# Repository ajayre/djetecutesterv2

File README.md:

# djetecutesterv2
D-Jetronic ECU Tester V2

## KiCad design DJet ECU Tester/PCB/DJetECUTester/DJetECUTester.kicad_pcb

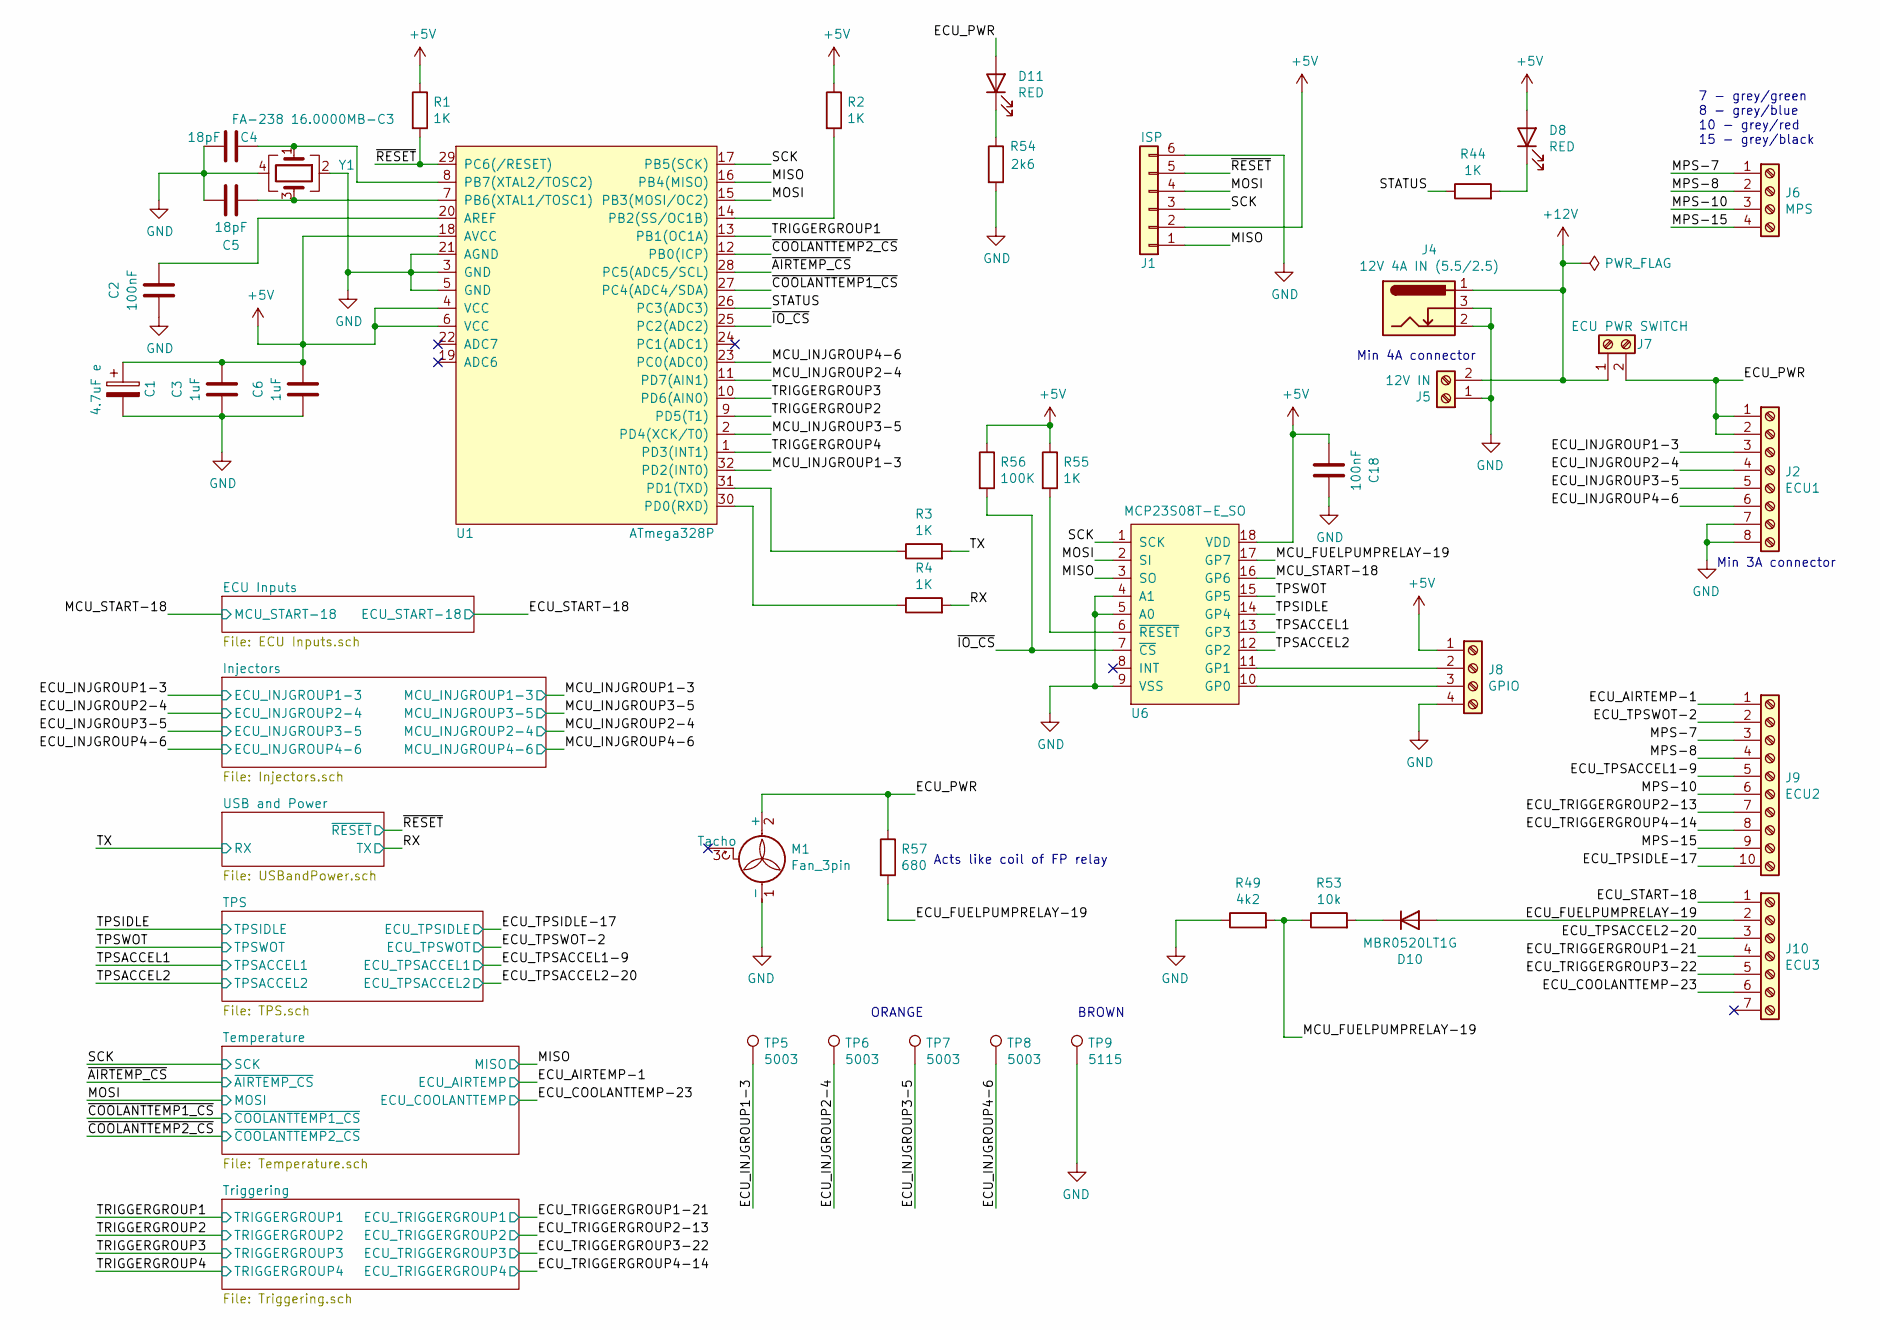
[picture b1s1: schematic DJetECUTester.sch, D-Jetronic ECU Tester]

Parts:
C1: 4.7uF e; CP_Elec_4x5.8
C2, C18: 100nF; C_0805_2012Metric
C3, C6: 1uF; C_0805_2012Metric
C4, C5: 18pF; C_0805_2012Metric
D8, D11: RED; LED_PLCC-2
D10: MBR0520LT1G; SOD-123
J1: ISP; PinHeader_2x03_P2.54mm_Vertical
J2: ECU1; PhoenixContact_COMBICON_PT_8
J4: 12V 4A IN (5.5/2.5); BarrelJack_Wuerth_6941xx301002
J5: 12V IN; PhoenixContact_COMBICON_MKDSN_2
J6: MPS; PhoenixContact_COMBICON_PT_4
J7: ECU PWR SWITCH; PhoenixContact_COMBICON_MKDSN_2
J8: GPIO; PhoenixContact_COMBICON_PT_4
J9: ECU2; PhoenixContact_COMBICON_PT_10
J10: ECU3; PhoenixContact_COMBICON_PT_7
M1: Fan_3pin; FanPinHeader_1x03_P2.54mm_Vertical
R1, R2, R3, R4, R44, R55: 1K; R_0805_2012Metric
R49: 4k2; R_0805_2012Metric
R53: 10k; R_0805_2012Metric
R54: 2k6; R_0805_2012Metric
R56: 100K; R_0805_2012Metric
R57: 680; R_1206_3216Metric
TP5, TP6, TP7, TP8: 5003; Keystone-Minature-Test-Point-Colored-500x-511x
TP9: 5115; Keystone-Minature-Test-Point-Colored-500x-511x
U1: ATmega328P; LQFP-32_7x7mm_P0.8mm
U6: MCP23S08T-E_SO; SOIC-18W_7.5x11.6mm_P1.27mm
Y1: FA-238 16.0000MB-C3; FA-238

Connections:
+5V: C1.1, C3.1, C6.1, C18.2, D8.2 (A), J1.2, J8.1, R1.1, R2.1, R55.1, R56.1, U1.4 (VCC), U1.6 (VCC), U1.18 (AVCC), U6.18 (VDD); also elsewhere on the board
+12V: J4.1, J5.2, J7.1; also elsewhere on the board
/ECU_AIRTEMP-1: J9.1; also elsewhere on the board
/ECU_COOLANTTEMP-23: J10.6; also elsewhere on the board
/ECU_FUELPUMPRELAY-19: D10.2 (A), J10.2, R57.2
/ECU_INJGROUP1-3: J2.3, TP5.1; also elsewhere on the board
/ECU_INJGROUP2-4: J2.4, TP6.1; also elsewhere on the board
/ECU_INJGROUP3-5: J2.5, TP7.1; also elsewhere on the board
/ECU_INJGROUP4-6: J2.6, TP8.1; also elsewhere on the board
/ECU_PWR: D11.2 (A), J2.1, J2.2, J7.2, M1.2 (+), R57.1
/ECU_START-18: J10.1; also elsewhere on the board
/ECU_TPSACCEL1-9: J9.5; also elsewhere on the board
/ECU_TPSACCEL2-20: J10.3; also elsewhere on the board
/ECU_TPSIDLE-17: J9.10; also elsewhere on the board
/ECU_TPSWOT-2: J9.2; also elsewhere on the board
/ECU_TRIGGERGROUP1-21: J10.4; also elsewhere on the board
/ECU_TRIGGERGROUP2-13: J9.7; also elsewhere on the board
/ECU_TRIGGERGROUP3-22: J10.5; also elsewhere on the board
/ECU_TRIGGERGROUP4-14: J9.8; also elsewhere on the board
/MCU_FUELPUMPRELAY-19: R49.2, R53.1, U6.17 (GP7)
/MCU_INJGROUP1-3: U1.32 (PD2(INT0)); also elsewhere on the board
/MCU_INJGROUP2-4: U1.11 (PD7(AIN1)); also elsewhere on the board
/MCU_INJGROUP3-5: U1.2 (PD4(XCK/T0)); also elsewhere on the board
/MCU_INJGROUP4-6: U1.23 (PC0(ADC0)); also elsewhere on the board
/MCU_START-18: U6.16 (GP6); also elsewhere on the board
/MISO: J1.1, U1.16 (PB4(MISO)), U6.3 (SO); also elsewhere on the board
/MOSI: J1.4, U1.15 (PB3(MOSI/OC2)), U6.2 (SI); also elsewhere on the board
/MPS-7: J6.1, J9.3
/MPS-8: J6.2, J9.4
/MPS-10: J6.3, J9.6
/MPS-15: J6.4, J9.9
/RX: R4.2; also elsewhere on the board
/SCK: J1.3, U1.17 (PB5(SCK)), U6.1 (SCK); also elsewhere on the board
/STATUS: R44.1, U1.26 (PC3(ADC3))
/TPSACCEL1: U6.13 (GP3); also elsewhere on the board
/TPSACCEL2: U6.12 (GP2); also elsewhere on the board
/TPSIDLE: U6.14 (GP4); also elsewhere on the board
/TPSWOT: U6.15 (GP5); also elsewhere on the board
/TRIGGERGROUP1: U1.13 (PB1(OC1A)); also elsewhere on the board
/TRIGGERGROUP2: U1.9 (PD5(T1)); also elsewhere on the board
/TRIGGERGROUP3: U1.10 (PD6(AIN0)); also elsewhere on the board
/TRIGGERGROUP4: U1.1 (PD3(INT1)); also elsewhere on the board
/TX: R3.2; also elsewhere on the board
/~AIRTEMP_CS: U1.28 (PC5(ADC5/SCL)); also elsewhere on the board
/~COOLANTTEMP1_CS: U1.27 (PC4(ADC4/SDA)); also elsewhere on the board
/~COOLANTTEMP2_CS: U1.12 (PB0(ICP)); also elsewhere on the board
/~IO_CS: R56.2, U1.25 (PC2(ADC2)), U6.7 (~CS)
/~RESET: J1.5, R1.2, U1.29 (PC6(/RESET)); also elsewhere on the board
GND: C1.2, C2.2, C3.2, C4.2, C5.1, C6.2, C18.1, J1.6, J2.7, J2.8, J4.2, J4.3, J5.1, J8.4, M1.1 (-), R49.1, R54.2, TP9.1, U1.3 (GND), U1.5 (GND), U1.21 (AGND), U6.4 (A1), U6.5 (A0), U6.9 (VSS), Y1.2, Y1.4; also elsewhere on the board
unnamed: C2.1, U1.20 (AREF)
unnamed: C4.1, U1.8 (PB7(XTAL2/TOSC2)), Y1.1
unnamed: C5.2, U1.7 (PB6(XTAL1/TOSC1)), Y1.3
unnamed: D8.1 (K), R44.2
unnamed: D10.1 (K), R53.2
unnamed: D11.1 (K), R54.1
unnamed: J8.2, U6.11 (GP1)
unnamed: J8.3, U6.10 (GP0)
unnamed: R2.2, U1.14 (PB2(SS/OC1B))
unnamed: R3.1, U1.31 (PD1(TXD))
unnamed: R4.1, U1.30 (PD0(RXD))
unnamed: R55.2, U6.6 (~RESET)

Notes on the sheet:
7 - grey/green 8 - grey/blue 10 - grey/red 15 - grey/black
BROWN
ORANGE
Min 4A connector
Min 3A connector
Acts like coil of FP relay

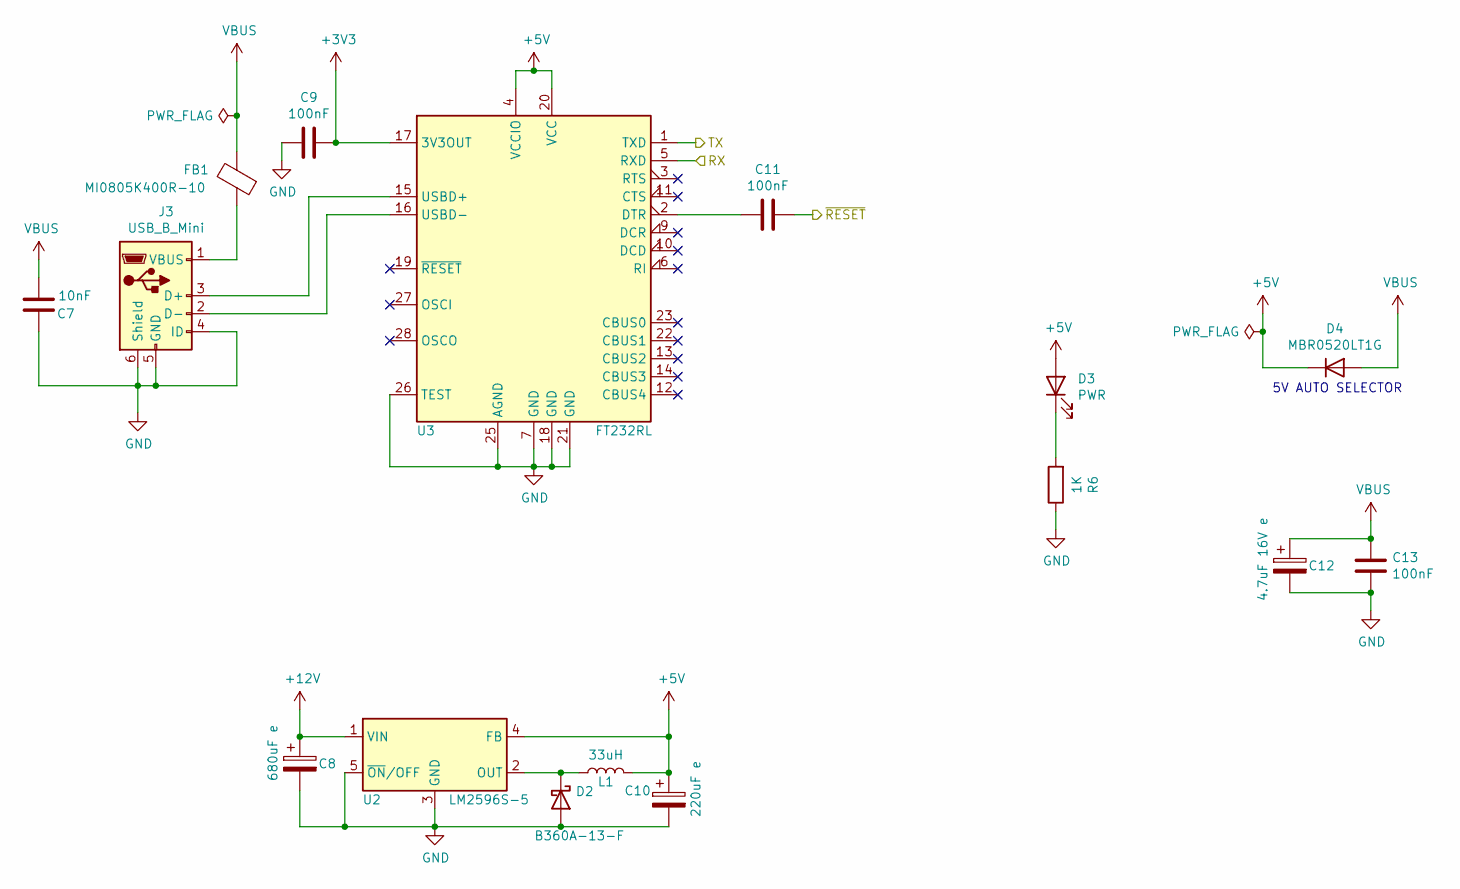
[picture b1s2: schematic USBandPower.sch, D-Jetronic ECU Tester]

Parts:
C7: 10nF; C_0805_2012Metric
C8: 680uF e; CP_Elec_10x10.5
C9, C11, C13: 100nF; C_0805_2012Metric
C10: 220uF e; CP_Elec_8x6.5
C12: 4.7uF 16V e; CP_Elec_4x5.8
D2: B360A-13-F; D_SMA
D3: PWR; LED_PLCC-2
D4: MBR0520LT1G; SOD-123
FB1: MI0805K400R-10; R_0805_2012Metric
J3: USB_B_Mini; USB_Mini-B_Wuerth_65100516121_Horizontal
L1: 33uH; Wurth-WE-LQS-Inductor
R6: 1K; R_0805_2012Metric
U2: LM2596S-5; TO-263-5_TabPin3
U3: FT232RL; SSOP-28_5.3x10.2mm_P0.65mm

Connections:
+3V3: C9.1, U3.17 (3V3OUT)
+5V: C10.1, D3.2 (A), D4.1 (K), L1.2, U2.4 (FB), U3.4 (VCCIO), U3.20 (VCC); also elsewhere on the board
+12V: C8.1, U2.1 (VIN); also elsewhere on the board
/RX: U3.1 (TXD); also elsewhere on the board
/TX: U3.5 (RXD); also elsewhere on the board
/~RESET: C11.1; also elsewhere on the board
GND: C7.1, C8.2, C9.2, C10.2, C12.2, C13.2, D2.2 (A), J3.4 (ID), J3.5 (GND), J3.6 (Shield), R6.1, U2.3 (GND), U2.5 (~ON~/OFF), U3.7 (GND), U3.18 (GND), U3.21 (GND), U3.25 (AGND), U3.26 (TEST); also elsewhere on the board
unnamed: C11.2, U3.2 (DTR)
unnamed: D2.1 (K), L1.1, U2.2 (OUT)
unnamed: D3.1 (K), R6.2
unnamed: FB1.1, J3.1 (VBUS)
unnamed: J3.2 (D-), U3.16 (USBD-)
unnamed: J3.3 (D+), U3.15 (USBD+)
VBUS: C7.2, C12.1, C13.1, D4.2 (A), FB1.2

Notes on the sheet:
5V AUTO SELECTOR

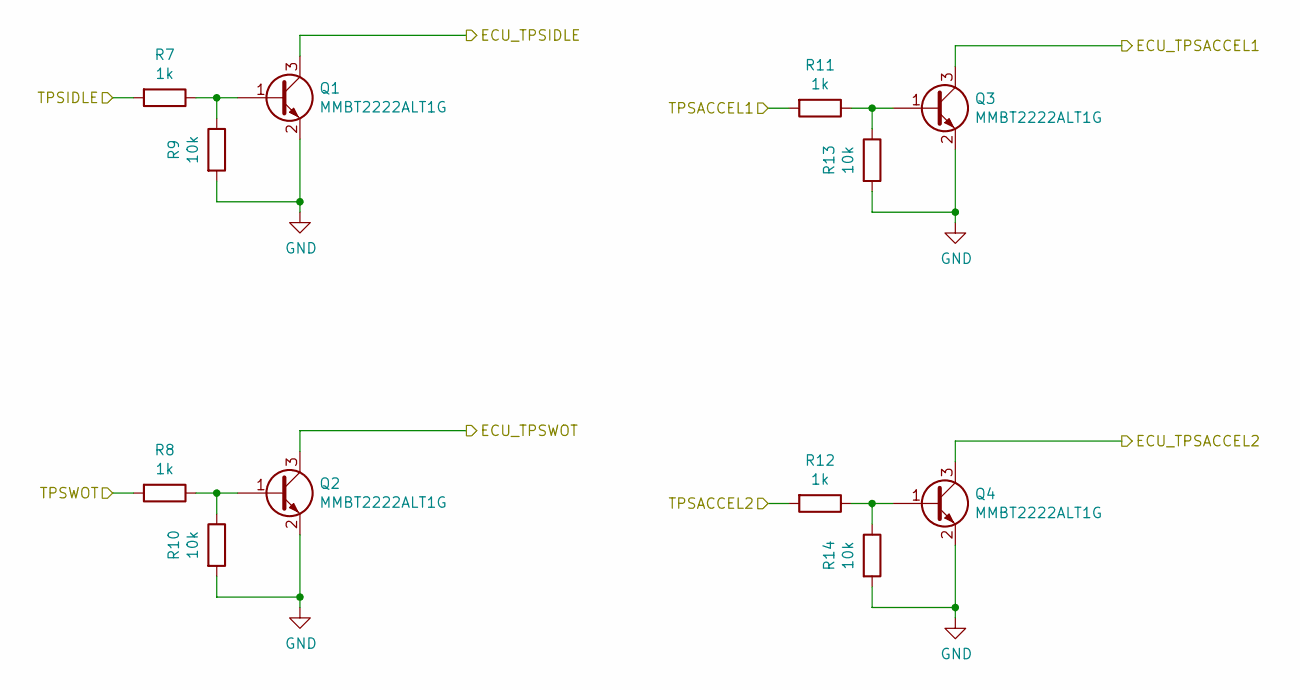
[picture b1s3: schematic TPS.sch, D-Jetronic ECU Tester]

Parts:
Q1, Q2, Q3, Q4: MMBT2222ALT1G; SOT-23
R7, R8, R11, R12: 1k; R_0805_2012Metric
R9, R10, R13, R14: 10k; R_0805_2012Metric

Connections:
/ECU_TPSACCEL1-9: Q3.3 (C); also elsewhere on the board
/ECU_TPSACCEL2-20: Q4.3 (C); also elsewhere on the board
/ECU_TPSIDLE-17: Q1.3 (C); also elsewhere on the board
/ECU_TPSWOT-2: Q2.3 (C); also elsewhere on the board
/TPSACCEL1: R11.2; also elsewhere on the board
/TPSACCEL2: R12.2; also elsewhere on the board
/TPSIDLE: R7.2; also elsewhere on the board
/TPSWOT: R8.2; also elsewhere on the board
GND: Q1.2 (E), Q2.2 (E), Q3.2 (E), Q4.2 (E), R9.2, R10.2, R13.2, R14.2; also elsewhere on the board
unnamed: Q1.1 (B), R7.1, R9.1
unnamed: Q2.1 (B), R8.1, R10.1
unnamed: Q3.1 (B), R11.1, R13.1
unnamed: Q4.1 (B), R12.1, R14.1

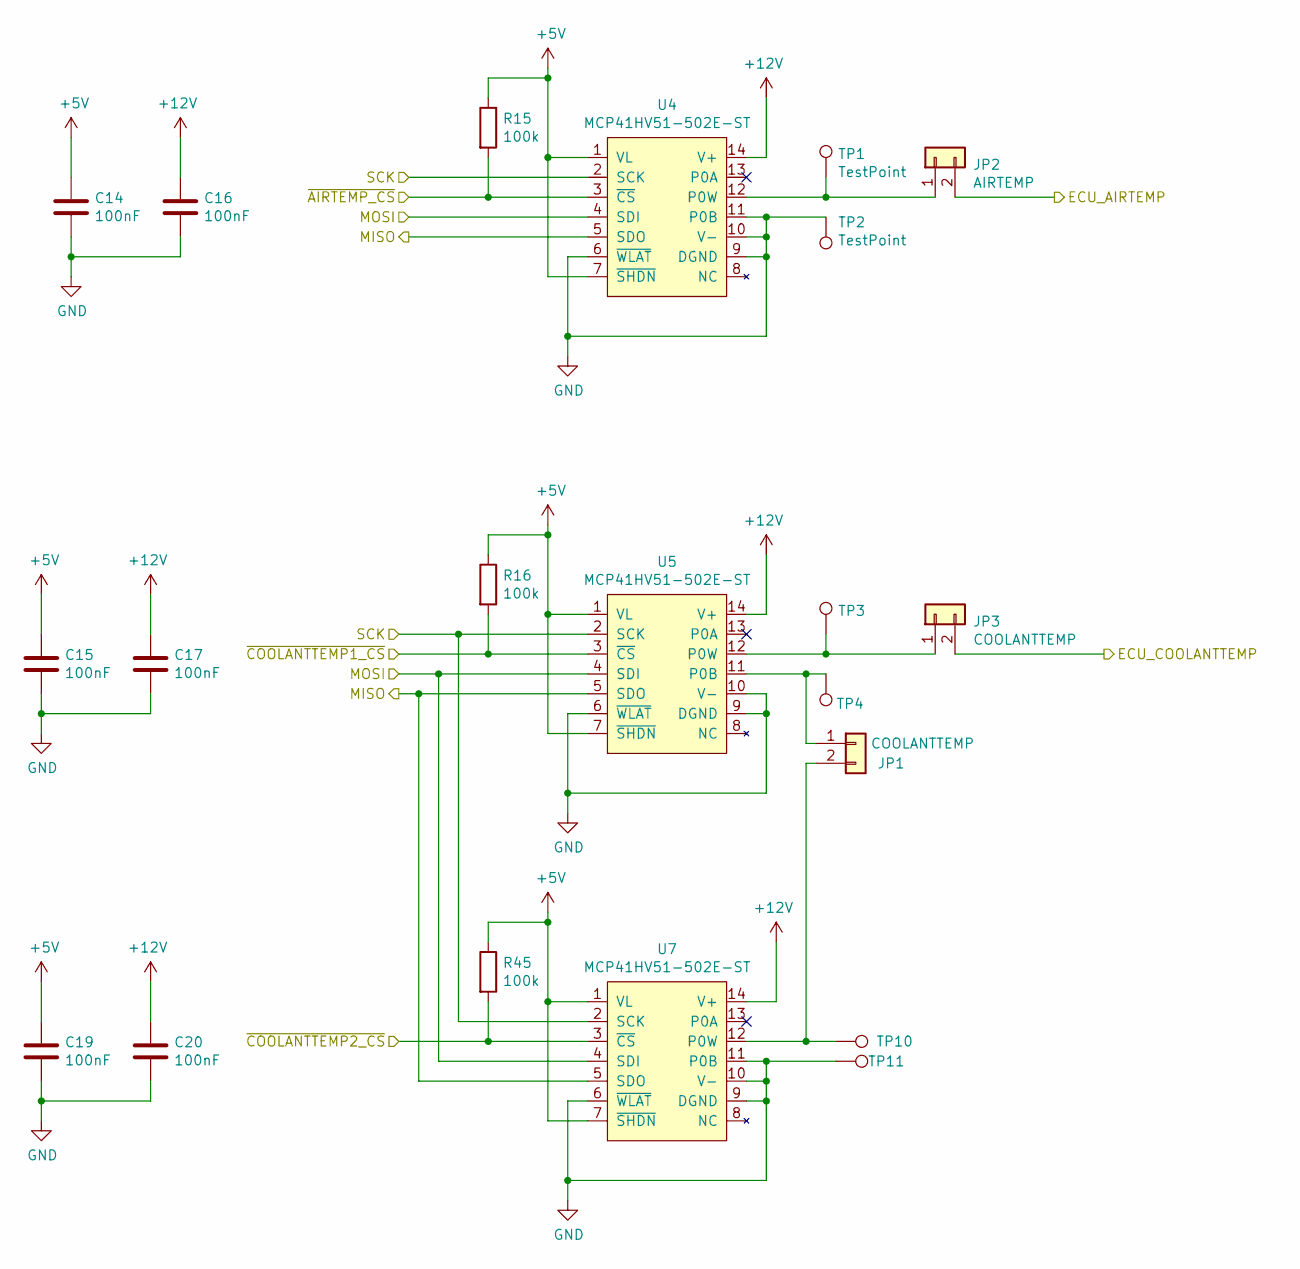
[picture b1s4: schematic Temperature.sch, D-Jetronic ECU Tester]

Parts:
C14, C15, C16, C17, C19, C20: 100nF; C_0805_2012Metric
JP1, JP3: COOLANTTEMP; PinHeader_2x01_P2.54mm_Vertical
JP2: AIRTEMP; PinHeader_2x01_P2.54mm_Vertical
R15, R16, R45: 100k; R_0805_2012Metric
TP1, TP2, TP3, TP4, TP10, TP11: TestPoint; TestPoint_Pad_D2.0mm
U4, U5, U7: MCP41HV51-502E-ST; TSSOP-14_4.4x5mm_P0.65mm

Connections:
+5V: C14.1, C15.1, C19.1, R15.1, R16.1, R45.1, U4.1 (VL), U4.7 (~SHDN), U5.1 (VL), U5.7 (~SHDN), U7.1 (VL), U7.7 (~SHDN); also elsewhere on the board
+12V: C16.1, C17.1, C20.1, U4.14 (V+), U5.14 (V+), U7.14 (V+); also elsewhere on the board
/ECU_AIRTEMP-1: JP2.2; also elsewhere on the board
/ECU_COOLANTTEMP-23: JP3.2; also elsewhere on the board
/MISO: U4.5 (SDO), U5.5 (SDO), U7.5 (SDO); also elsewhere on the board
/MOSI: U4.4 (SDI), U5.4 (SDI), U7.4 (SDI); also elsewhere on the board
/SCK: U4.2 (SCK), U5.2 (SCK), U7.2 (SCK); also elsewhere on the board
/~AIRTEMP_CS: R15.2, U4.3 (~CS); also elsewhere on the board
/~COOLANTTEMP1_CS: R16.2, U5.3 (~CS); also elsewhere on the board
/~COOLANTTEMP2_CS: R45.2, U7.3 (~CS); also elsewhere on the board
GND: C14.2, C15.2, C16.2, C17.2, C19.2, C20.2, TP2.1, TP11.1, U4.6 (~WLAT), U4.9 (DGND), U4.10 (V-), U4.11 (P0B), U5.6 (~WLAT), U5.9 (DGND), U5.10 (V-), U7.6 (~WLAT), U7.9 (DGND), U7.10 (V-), U7.11 (P0B); also elsewhere on the board
unnamed: JP1.1, TP4.1, U5.11 (P0B)
unnamed: JP1.2, TP10.1, U7.12 (P0W)
unnamed: JP2.1, TP1.1, U4.12 (P0W)
unnamed: JP3.1, TP3.1, U5.12 (P0W)

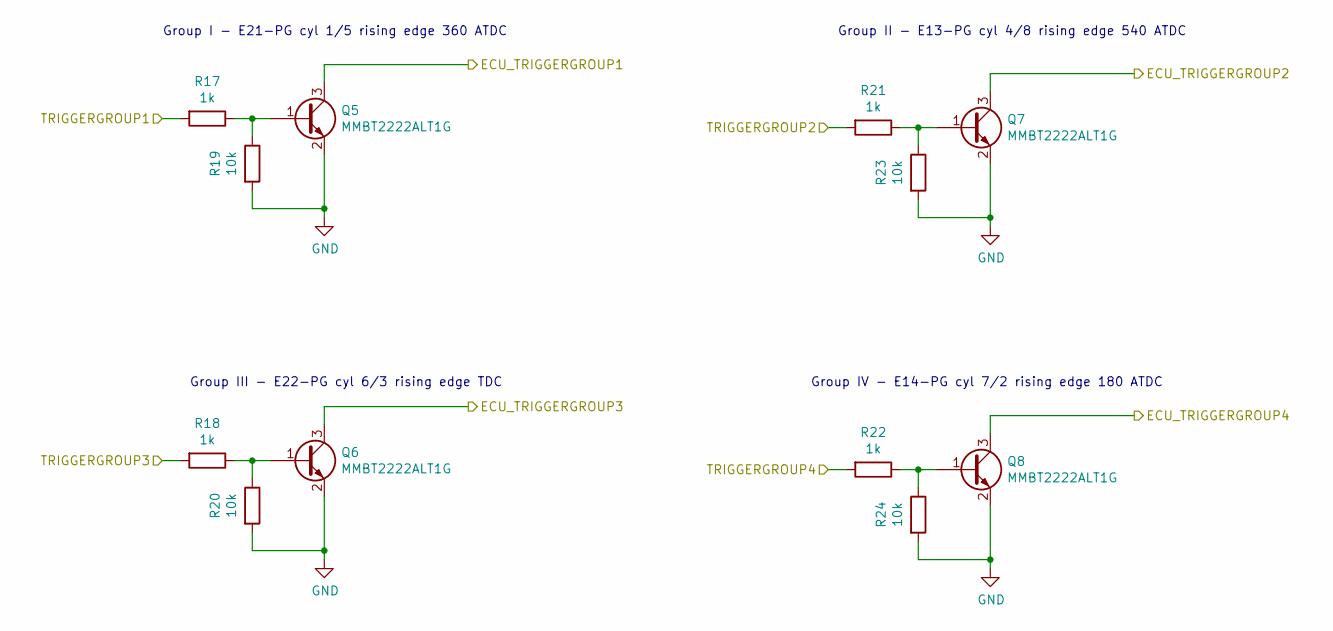
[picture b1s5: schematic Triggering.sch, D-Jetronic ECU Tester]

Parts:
Q5, Q6, Q7, Q8: MMBT2222ALT1G; SOT-23
R17, R18, R21, R22: 1k; R_0805_2012Metric
R19, R20, R23, R24: 10k; R_0805_2012Metric

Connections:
/ECU_TRIGGERGROUP1-21: Q5.3 (C); also elsewhere on the board
/ECU_TRIGGERGROUP2-13: Q7.3 (C); also elsewhere on the board
/ECU_TRIGGERGROUP3-22: Q6.3 (C); also elsewhere on the board
/ECU_TRIGGERGROUP4-14: Q8.3 (C); also elsewhere on the board
/TRIGGERGROUP1: R17.2; also elsewhere on the board
/TRIGGERGROUP2: R21.2; also elsewhere on the board
/TRIGGERGROUP3: R18.2; also elsewhere on the board
/TRIGGERGROUP4: R22.2; also elsewhere on the board
GND: Q5.2 (E), Q6.2 (E), Q7.2 (E), Q8.2 (E), R19.2, R20.2, R23.2, R24.2; also elsewhere on the board
unnamed: Q5.1 (B), R17.1, R19.1
unnamed: Q6.1 (B), R18.1, R20.1
unnamed: Q7.1 (B), R21.1, R23.1
unnamed: Q8.1 (B), R22.1, R24.1

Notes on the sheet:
Group I - E21-PG cyl 1/5 rising edge 360 ATDC
Group II - E13-PG cyl 4/8 rising edge 540 ATDC
Group III - E22-PG cyl 6/3 rising edge TDC
Group IV - E14-PG cyl 7/2 rising edge 180 ATDC

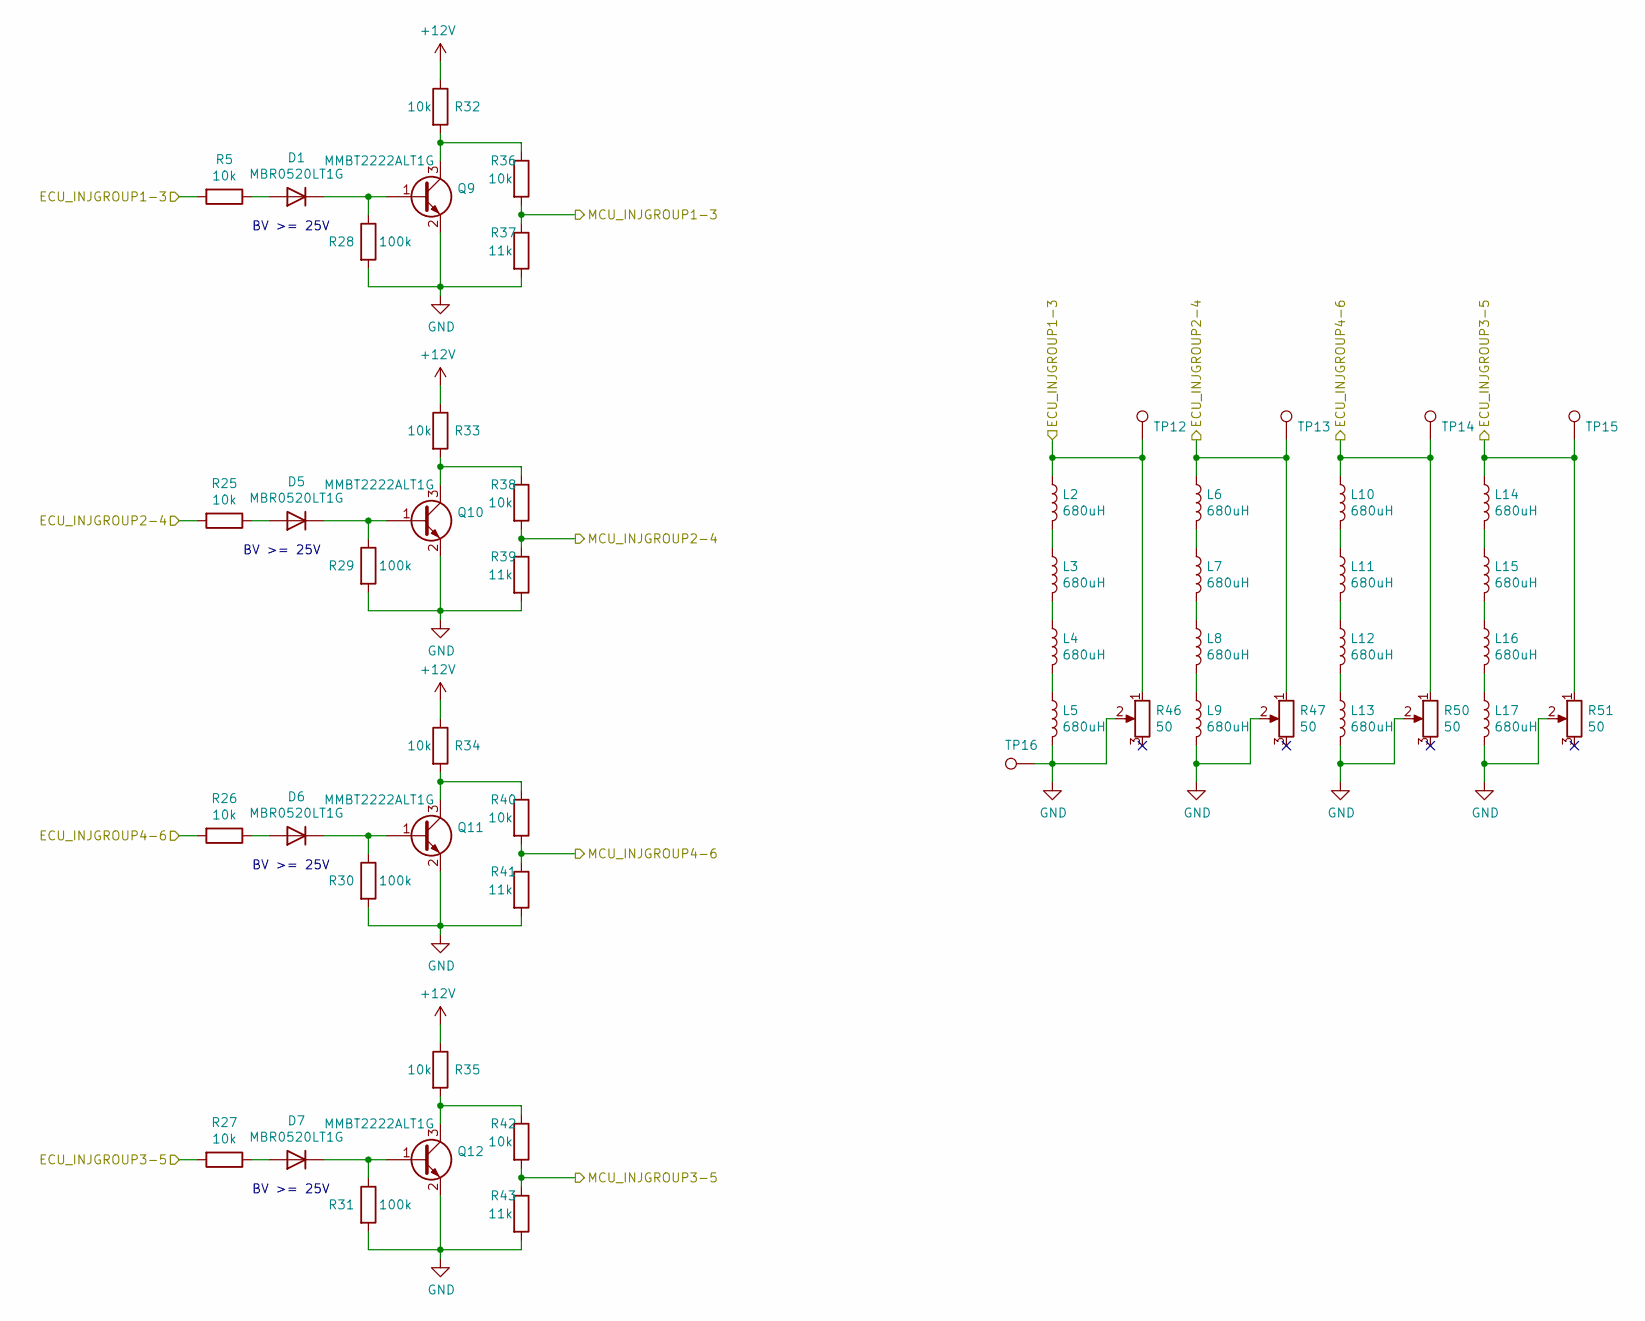
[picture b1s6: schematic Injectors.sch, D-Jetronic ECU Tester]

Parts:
D1, D5, D6, D7: MBR0520LT1G; SOD-123
L2, L3, L4, L5, L6, L7, L8, L9, L10, L11, L12, L13, L14, L15, L16, L17: 680uH; Inductor-MSS1210-684KED
Q9, Q10, Q11, Q12: MMBT2222ALT1G; SOT-23
R5, R25, R26, R27, R32, R33, R34, R35, R36, R38, R40, R42: 10k; R_0805_2012Metric
R28, R29, R30, R31: 100k; R_0805_2012Metric
R37, R39, R41, R43: 11k; R_0805_2012Metric
R46, R47, R50, R51: 50; Potentometer_Bourns_PV36W
TP12, TP13, TP14, TP15, TP16: TestPoint; TestPoint_Pad_D2.0mm

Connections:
+12V: R32.1, R33.1, R34.1, R35.1; also elsewhere on the board
/ECU_INJGROUP1-3: L2.1, R5.2, R46.1, TP12.1; also elsewhere on the board
/ECU_INJGROUP2-4: L6.1, R25.2, R47.1, TP13.1; also elsewhere on the board
/ECU_INJGROUP3-5: L14.1, R27.2, R51.1, TP15.1; also elsewhere on the board
/ECU_INJGROUP4-6: L10.1, R26.2, R50.1, TP14.1; also elsewhere on the board
/MCU_INJGROUP1-3: R36.2, R37.1; also elsewhere on the board
/MCU_INJGROUP2-4: R38.2, R39.1; also elsewhere on the board
/MCU_INJGROUP3-5: R42.2, R43.1; also elsewhere on the board
/MCU_INJGROUP4-6: R40.2, R41.1; also elsewhere on the board
GND: L5.2, L9.2, L13.2, L17.2, Q9.2 (E), Q10.2 (E), Q11.2 (E), Q12.2 (E), R28.2, R29.2, R30.2, R31.2, R37.2, R39.2, R41.2, R43.2, R46.2, R47.2, R50.2, R51.2, TP16.1; also elsewhere on the board
unnamed: D1.1 (K), Q9.1 (B), R28.1
unnamed: D1.2 (A), R5.1
unnamed: D5.1 (K), Q10.1 (B), R29.1
unnamed: D5.2 (A), R25.1
unnamed: D6.1 (K), Q11.1 (B), R30.1
unnamed: D6.2 (A), R26.1
unnamed: D7.1 (K), Q12.1 (B), R31.1
unnamed: D7.2 (A), R27.1
unnamed: L2.2, L3.1
unnamed: L3.2, L4.1
unnamed: L4.2, L5.1
unnamed: L6.2, L7.1
unnamed: L7.2, L8.1
unnamed: L8.2, L9.1
unnamed: L10.2, L11.1
unnamed: L11.2, L12.1
unnamed: L12.2, L13.1
unnamed: L14.2, L15.1
unnamed: L15.2, L16.1
unnamed: L16.2, L17.1
unnamed: Q9.3 (C), R32.2, R36.1
unnamed: Q10.3 (C), R33.2, R38.1
unnamed: Q11.3 (C), R34.2, R40.1
unnamed: Q12.3 (C), R35.2, R42.1

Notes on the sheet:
BV >= 25V

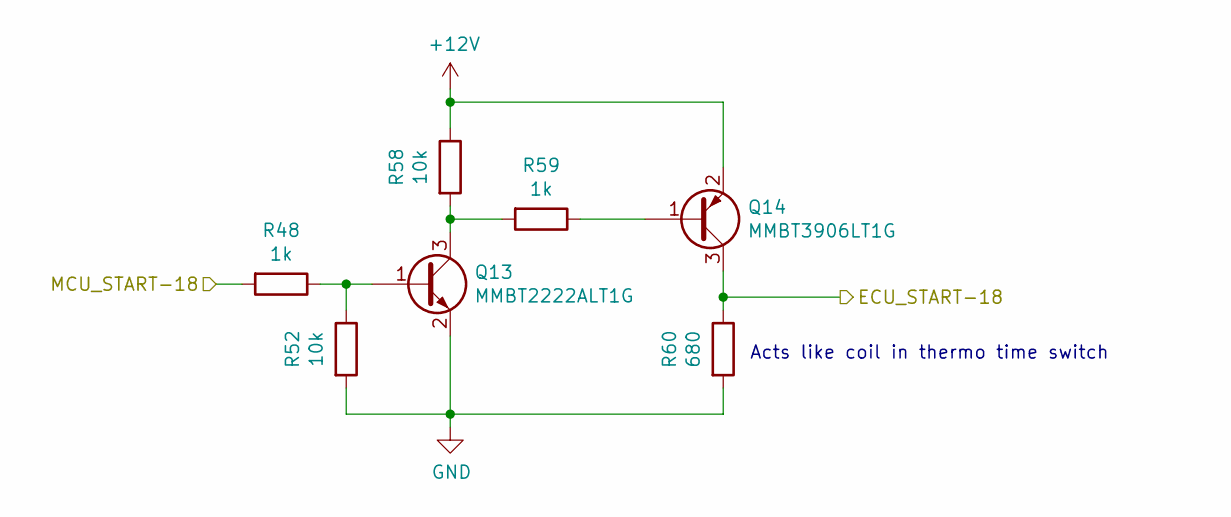
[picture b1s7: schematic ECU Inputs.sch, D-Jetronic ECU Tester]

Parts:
Q13: MMBT2222ALT1G; SOT-23
Q14: MMBT3906LT1G; SOT-23
R48, R59: 1k; R_0805_2012Metric
R52, R58: 10k; R_0805_2012Metric
R60: 680; R_1206_3216Metric

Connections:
+12V: Q14.2 (E), R58.1; also elsewhere on the board
/ECU_START-18: Q14.3 (C), R60.1; also elsewhere on the board
/MCU_START-18: R48.2; also elsewhere on the board
GND: Q13.2 (E), R52.2, R60.2; also elsewhere on the board
unnamed: Q13.1 (B), R48.1, R52.1
unnamed: Q13.3 (C), R58.2, R59.2
unnamed: Q14.1 (B), R59.1

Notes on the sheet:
Acts like coil in thermo time switch

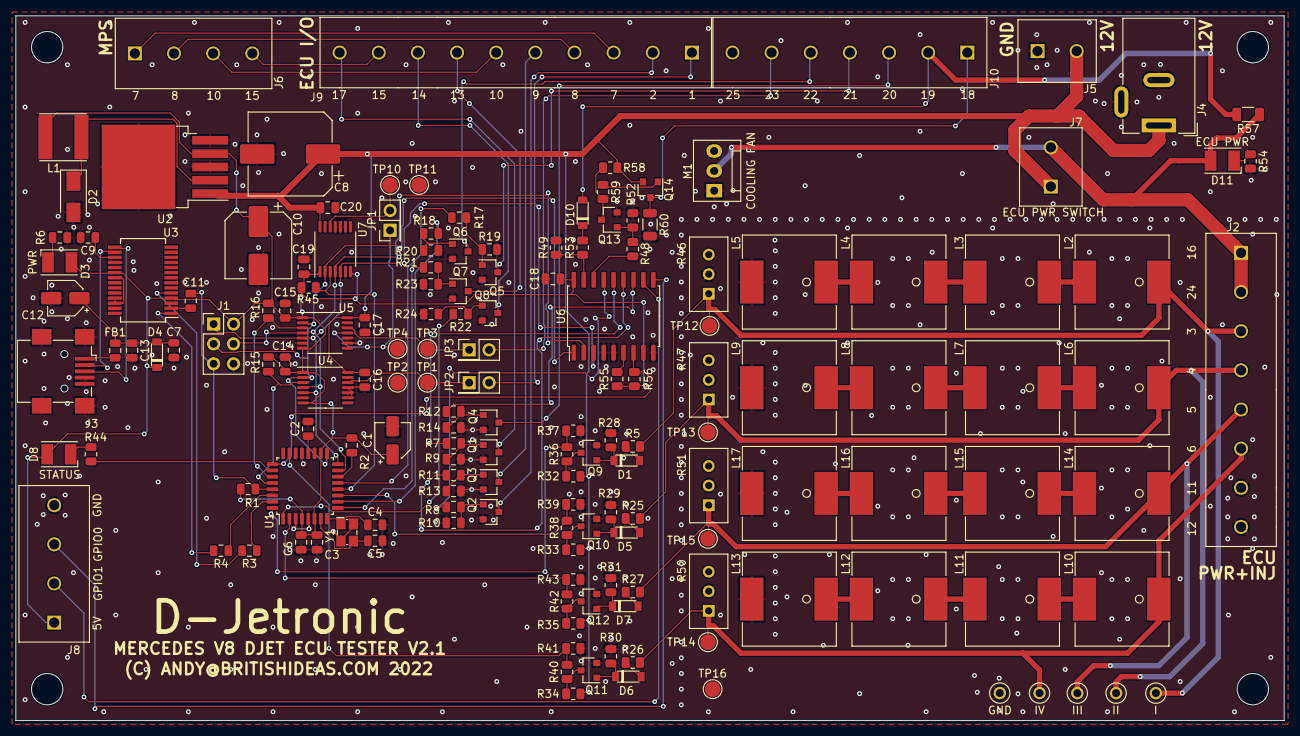
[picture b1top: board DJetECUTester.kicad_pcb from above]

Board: 2 copper layers, 162.0 x 90.0 mm, 160 parts (0 on the bottom side), 108 nets.

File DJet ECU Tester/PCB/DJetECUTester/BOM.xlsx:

Item | Qty | Reference(s) | Value | LibPart | Footprint | manf# | manf2#
1 | 1 | C1 | 4.7uF e | Device:CP | Capacitor_SMD:CP_Elec_4x5.8
2 | 11 | C2, C9, C11, C13, C14, C15, C16, C17, C18, C19, C20 | 100nF | Device:C | Capacitor_SMD:C_0805_2012Metric
3 | 2 | C3, C6 | 1uF | Device:C | Capacitor_SMD:C_0805_2012Metric
4 | 2 | C4, C5 | 18pF | Device:C | Capacitor_SMD:C_0805_2012Metric
5 | 1 | C7 | 10nF | Device:C | Capacitor_SMD:C_0805_2012Metric
6 | 1 | C8 | 680uF e | Device:CP | Capacitor_SMD:CP_Elec_10x10.5
7 | 1 | C10 | 220uF e | Device:CP | Capacitor_SMD:CP_Elec_8x6.5
8 | 1 | C12 | 4.7uF 16V e | Device:CP | Capacitor_SMD:CP_Elec_4x5.8
9 | 7 | D1, D4, D5, D6, D7, D9, D10 | MBR0520LT1G | Device:D | Britishideas:SOD-123 | MBR0520LT1G
10 | 1 | D2 | B360A-13-F | Device:D_Schottky | Diode_SMD:D_SMA | B360A-13-F
11 | 1 | D3 | PWR | Device:LED | LED_SMD:LED_PLCC-2
12 | 2 | D8, D11 | RED | Device:LED | LED_SMD:LED_PLCC-2
13 | 1 | FB1 | MI0805K400R-10 | Device:Ferrite_Bead | Resistor_SMD:R_0805_2012Metric | MI0805K400R-10
15 | 1 | J2 | ECU1 | Connector:Screw_Terminal_01x08 | Britishideas:PhoenixContact_COMBICON_PT_8 | 1935831
16 | 1 | J3 | USB_B_Mini | DJetECUTester-rescue:USB_B_Mini-Connector | Connector_USB:USB_Mini-B_Wuerth_65100516121_Horizontal | 65100516121
17 | 1 | J4 | 12V 4A IN (5.5/2.5) | Connector:Barrel_Jack_Switch | Connector_BarrelJack:BarrelJack_Wuerth_6941xx301002 | 694108000000
18 | 1 | J5 | 12V IN | Connector:Screw_Terminal_01x02 | Britishideas:PhoenixContact_COMBICON_MKDSN_2 | 1729018
19 | 1 | J6 | MPS | Connector:Screw_Terminal_01x04 | Britishideas:PhoenixContact_COMBICON_PT_4 | 1935792
20 | 2 | J7, J8 | Conn_01x01 | Connector_Generic:Conn_01x01 | Britishideas:tabconnector-63849-1 | 63849-1
21 | 1 | J9 | ECU2 | Connector:Screw_Terminal_01x10 | Britishideas:PhoenixContact_COMBICON_PT_10 | 1935242
22 | 1 | J10 | ECU3 | Connector:Screw_Terminal_01x07 | Britishideas:PhoenixContact_COMBICON_PT_7 | 1935213
25 | 1 | L1 | 33uH | Device:L | Britishideas:Wurth-WE-LQS-Inductor | 74404063330
26 | 16 | L2, L3, L4, L5, L6, L7, L8, L9, L10, L11, L12, L13, L14, L15, L16, L17 | 680uH | Device:L | Britishideas:Inductor-MSS1210-684KED | MSS1210-684KED
27 | 12 | Q1, Q2, Q3, Q4, Q5, Q6, Q7, Q8, Q9, Q10, Q11, Q12 | MMBT2222ALT1G | Transistor_BJT:MMBT3904 | Package_TO_SOT_SMD:SOT-23 | MMBT2222ALT1G
28 | 6 | R1, R2, R3, R4, R6, R44 | 1K | Device:R | Resistor_SMD:R_0805_2012Metric
29 | 22 | R5, R9, R10, R13, R14, R19, R20, R23, R24, R25, R26, R27, R32, R33, R34, R35, R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 | 10k | Device:R | Resistor_SMD:R_0805_2012Metric
30 | 8 | R7, R8, R11, R12, R17, R18, R21, R22 | 1k | Device:R | Resistor_SMD:R_0805_2012Metric
31 | 7 | R15, R16, R28, R29, R30, R31, R45 | 100k | Device:R | Resistor_SMD:R_0805_2012Metric
32 | 4 | R37, R39, R41, R43 | 11k | Device:R | Resistor_SMD:R_0805_2012Metric
33 | 4 | R46, R47, R50, R51 | 50 | Device:R_POT | Britishideas:Potentometer_Bourns_PV36W | PV36W500C01B00
34 | 2 | R48, R49 | 4k2 | Device:R | Resistor_SMD:R_0805_2012Metric
35 | 1 | R54 | 2k6 | Device:R | Resistor_SMD:R_0805_2012Metric
36 | 1 | U1 | ATmega328P | BritishIdeas:ATmega328P | Package_QFP:LQFP-32_7x7mm_P0.8mm | ATMEGA328P-AUR
37 | 1 | U2 | LM2596S-5 | Regulator_Switching:LM2596S-5 | Package_TO_SOT_SMD:TO-263-5_TabPin3 | LM2596S-5.0/NOPB
38 | 1 | U3 | FT232RL | Interface_USB:FT232RL | Package_SO:SSOP-28_5.3x10.2mm_P0.65mm | FT232RL-REEL
39 | 3 | U4, U5, U7 | MCP41HV51-502E-ST | BritishIdeas:MCP41HV51-502E-ST | Package_SO:TSSOP-14_4.4x5mm_P0.65mm | MCP41HV51-502E/ST | MCP41HV31-502E/ST
40 | 1 | U6 | MCP23S08T-E_SO | BritishIdeas:MCP23S08T-E_SO | Package_SO:SOIC-18W_7.5x11.6mm_P1.27mm
41 | 1 | Y1 | FA-238 16.0000MB-C3 | Device:Crystal_GND24 | Britishideas:FA-238 | FA-238 16.0000MB-C3
42 | 4 |  | 5194TR
43 | 1 |  | 5195TR

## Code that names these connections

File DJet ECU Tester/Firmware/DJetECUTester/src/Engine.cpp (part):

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#define DYNAMIC_TEST_STATUS_PERIOD_MS 30

// mcu pins
#define PIN_STATUS_LED     A3  // PC3
#define PIN_AIRTEMPCS      A5  // PC5
#define PIN_COOLANTTEMPCS1 A4  // PC4
#define PIN_COOLANTTEMPCS2 8   // PB0
#define PIN_IOCS           A2  // PC2

// io expander pins
#define PIN_TPSACCEL2 2
#define PIN_TPSACCEL1 3
#define PIN_TPSIDLE   4
#define PIN_TPSWOT    5
#define PIN_START     6
#define PIN_FUELPUMP  7

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#define PORT_TRIGGERGROUP3 PORTD
#define PORT_TRIGGERGROUP4 PORTD

#define PIN_TRIGGERGROUP1 1
#define PIN_TRIGGERGROUP2 5
#define PIN_TRIGGERGROUP3 6
#define PIN_TRIGGERGROUP4 3

#define DIR_TRIGGERGROUP1 DDRB
#define DIR_TRIGGERGROUP2 DDRD
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#define STATUS_LED_OFF          digitalWrite(PIN_STATUS_LED, HIGH);
#define IS_STATUS_LED_ON        (digitalRead(PIN_STATUS_LED) == 1 ? FALSE : TRUE)

#define TPS_WOT                 IOExpander.write(PIN_TPSWOT, 1);
#define TPS_NOTWOT              IOExpander.write(PIN_TPSWOT, 0);

#define TPS_IDLE                IOExpander.write(PIN_TPSIDLE, 1);
#define TPS_NOTIDLE             IOExpander.write(PIN_TPSIDLE, 0);

#define TPS_ACCEL1_ASSERT       IOExpander.write(PIN_TPSACCEL1, 1);
#define TPS_ACCEL1_DEASSERT     IOExpander.write(PIN_TPSACCEL1, 0);

#define TPS_ACCEL2_ASSERT       IOExpander.write(PIN_TPSACCEL2, 1);
#define TPS_ACCEL2_DEASSERT     IOExpander.write(PIN_TPSACCEL2, 0);

#define AIRTEMPCS_DEASSERT      digitalWrite(PIN_AIRTEMPCS,      HIGH);
#define COOLANTTEMPCS1_DEASSERT digitalWrite(PIN_COOLANTTEMPCS1, HIGH);
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
#define FUEL_PUMP_ACTIVE        !IOExpander.read(PIN_FUELPUMP)

#define TRIGGERGROUP1_HIGH (PORT_TRIGGERGROUP1 &= ~(1 << PIN_TRIGGERGROUP1))
#define TRIGGERGROUP1_LOW  (PORT_TRIGGERGROUP1 |=  (1 << PIN_TRIGGERGROUP1))
#define TRIGGERGROUP2_HIGH (PORT_TRIGGERGROUP2 &= ~(1 << PIN_TRIGGERGROUP2))
#define TRIGGERGROUP2_LOW  (PORT_TRIGGERGROUP2 |=  (1 << PIN_TRIGGERGROUP2))
#define TRIGGERGROUP3_HIGH (PORT_TRIGGERGROUP3 &= ~(1 << PIN_TRIGGERGROUP3))
#define TRIGGERGROUP3_LOW  (PORT_TRIGGERGROUP3 |=  (1 << PIN_TRIGGERGROUP3))
#define TRIGGERGROUP4_HIGH (PORT_TRIGGERGROUP4 &= ~(1 << PIN_TRIGGERGROUP4))
#define TRIGGERGROUP4_LOW  (PORT_TRIGGERGROUP4 |=  (1 << PIN_TRIGGERGROUP4))

#define ASSERT   1
#define DEASSERT 0
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  // set up outputs
  pinMode(PIN_STATUS_LED,    OUTPUT);
  STATUS_LED_OFF;
  DIR_TRIGGERGROUP1 |= (1 << PIN_TRIGGERGROUP1);
  TRIGGERGROUP1_HIGH;
  DIR_TRIGGERGROUP2 |= (1 << PIN_TRIGGERGROUP2);
  TRIGGERGROUP2_HIGH;
  DIR_TRIGGERGROUP3 |= (1 << PIN_TRIGGERGROUP3);
  TRIGGERGROUP3_HIGH;
  DIR_TRIGGERGROUP4 |= (1 << PIN_TRIGGERGROUP4);
  TRIGGERGROUP4_HIGH;
  pinMode(PIN_AIRTEMPCS,     OUTPUT);
  AIRTEMPCS_DEASSERT;
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  CoolantTempPot1 = new MCP4XXX(PIN_COOLANTTEMPCS1, icecave::arduino::MCP4XXX::pot_0, icecave::arduino::MCP4XXX::res_7bit);
  CoolantTempPot2 = new MCP4XXX(PIN_COOLANTTEMPCS2, icecave::arduino::MCP4XXX::pot_0, icecave::arduino::MCP4XXX::res_7bit);

  IOExpander.pinMode(PIN_TPSACCEL2, OUTPUT);
  IOExpander.pinMode(PIN_TPSACCEL1, OUTPUT);
  IOExpander.pinMode(PIN_TPSIDLE,   OUTPUT);
  IOExpander.pinMode(PIN_TPSWOT,    OUTPUT);
  IOExpander.pinMode(PIN_START,     OUTPUT);
  IOExpander.pinMode(PIN_FUELPUMP,  INPUT);
  IOExpander.setPullup((1 << PIN_TPSACCEL2) | (1 << PIN_TPSACCEL1) | (1 << PIN_TPSIDLE) | (1 << PIN_TPSWOT));
  START_DEASSERT;

  // set up pulse generator
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
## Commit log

2022-09-18 Forked from djetecutester.
2022-09-18 Working on new schematic diagram.
2022-09-18 Removed unused files.
2022-09-18 Added IO multiplexer. Working on additional coolant temperature options. Added status LED back in.
2022-09-23 Completed new schematic.
2022-09-23 Work in progress.
2022-09-26 Working on new PCB.
2022-09-26 Initial routing completed.
2022-09-27 Tweaked PCB layout, added basic ground stitching vias. Regenerated BOM.
2022-09-27 Added test points from trimpots. Added ground stitching vias around inductors.
2022-09-28 Completed layout. Added pull up resistors. Added ground stitching vias. Removed unused datasheets. Updated PDF schematic. Added manufacturing files. Added 3D model.
2022-09-28 Zipped manufacturing files.
2022-09-28 Added Alibre Design 3D model.
2022-09-29 Added case. Added switch datasheets. Started work on firmware.
2022-09-30 Working on case.
2022-10-05 Working on integrating Firmata.
2022-10-05 Completed first version of case.
2022-10-05 Working on PC application.
2022-10-06 Working on PC application and firmware.
2022-10-06 Working on user interface. Added display of all four pulse widths.
2022-10-06 Reports all four pulse widths.
2022-10-06 Working on user interface.
2022-10-06 Added livecharts.
2022-10-08 Working on firmware and PC application.
2022-10-08 Cleanup
2022-10-08 Clean up of case top.
2022-10-09 Working on temperature support. Improved case design to give access to screw terminals and injector tuning.
2022-10-09 Completed temperature sensors. Removed cranking. Added pressure/vacuum display.
2022-10-10 Added support for IO expander. Minor cleanup.
2022-10-10 Added framework for reporting and display of ECU outputs
2022-10-10 Cleanup. Added framework for periodic measurement and display of ECU outputs.
2022-10-14 Added support for reading pulse widths.
2022-10-14 Added ventilation holes to case. TPS enrichment pulses now working.
2022-10-15 Updated PCB to add resistor for fuel pump relay. Swapped trigger group signals 2 and 3 back to how they should be. Fuel pump now reports off when engine stopped.
2022-10-15 Changed start signal from ECU output to ECU input.
2022-10-15 Added connector for cooling fan.
2022-10-15 Added screw block for connecting ECU power switch.
2022-10-15 Added more robust test points. Added GPIO connector.
2022-10-16 Added ground vias. Regenerated 3D model of PCB. Minor improvement to case top.
2022-10-16 Regenerated PCB manufacturing files. Regenerated PDF Schematic.pdf
2022-10-16 Firmware is now version 2.1 to match new PCB. Now allows engine speed down to 0 RPM. Changed cold start to start signal.
2022-10-17 Added cranking with unstable RPM. Changed default cranking RPM to 215 based on test results.
2022-10-17 Added documentation. Firmware simulation sets pulse widths to zero when engine is off.
2022-10-17 Improvements to gallery. Working on dynamic UI.
2022-10-18 Working on dynamic testing.
2022-10-18 Renamed to DJetronic Studio. Added new icon.
2022-10-18 Renamed to DJetronic Studio.
2022-10-19 Working on dynamic testing - starting, stopping and cancelling. Fixed bugs with dynamic testing calculation for speed. Added air temp to dynamic test.
2022-10-20 Added UI to connect to simulator instead of tester.
2022-10-20 Completed first attempt at dynamic testing. Disabled simulation and automated testing options.
2022-10-20 Changed to 64-bit application. Added installer with release notes. Deleted old license.
2022-10-20 Added new license.
2022-10-21 Working on charting. Added UI for CSV export - not functional.
2022-10-21 Added license to about window.
2022-10-22 Added more icons and UI elements. Working on charting. Added CSV export of data buffer.
2022-10-23 Working on charting.
2022-10-23 Working on chart.
2022-10-24 Swapped trigger outputs back as V2.1 PCB does not have the signals swapped. Changed preset cranking speed to 50RPM to demonstrate start signal operation. Improvements to charting.
2022-10-25 Updated to beta 514 of LiveCharts2. Added chart title.
2022-10-26 Added realistic switch to case model. Added Keyshot file.
2022-10-27 Version 1.0.0.0 Rebuilt.
2022-11-01 Remove DJetronic Studio - now in it's own repo.
2022-11-04 Added reporting of the product unique id.
2022-11-04 Added missing file.
2022-11-05 Fixed bug with reporting product UID. Added libraries.
2022-11-05 Now reports product ID and firmware version.
2022-12-10 Added firmware release.
2022-12-16 Ramps down throttle. Detects when injector pulses have stopped.
2022-12-20 Fixed bug with command to start dynamic tests. Added throttle to dynamic tests. Added start conditions for all variables to dynamic tests. Improvements to "no pulse" detection.
2022-12-21 Added support for removing foot from throttle.
2022-12-28 Updated symbols from rescue to library.
2023-01-11 Version 2.3
